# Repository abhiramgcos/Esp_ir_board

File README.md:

# ESP32 IR Blaster

**A Wi-Fi infrared remote you build yourself.** It learns the buttons of your existing remotes (TV, A/C, set-top
box, fan, LED strip) and plays them back from your phone, a script or Home Assistant.

<sub>KiCad 3D render of the v2.1.4 board, not a photo. The USB-C model is a stand-in for the HRO part.</sub>

## Features

* **Strong IR output:** two 940 nm LEDs driven at ~100 mA through a MOSFET, ≈8–10 m line-of-sight range.
* **On-board receiver:** a 38 kHz TSOP38238 for learning codes. The receiver and both IR LEDs face out of
  the same board edge, so one side of the board points at your devices.
* **One-click flashing:** USB-C with a CH340C USB-serial chip and auto-reset; no buttons, no adapter.
* **Ready-to-use firmware:**
  * web UI, REST API, captive-portal Wi-Fi setup, OTA updates;
  * stores decoded, A/C and raw codes.
* **Home Assistant via ESPHome:** native buttons, a climate entity for A/C, and send-code actions, from a
  prebuilt image you adopt in one click.
* **Robust power:** USB ESD protection, resettable fuse, diode-OR'd external 5 V input, 600 mA LDO.
* **Expansion:** I²C with pull-ups plus 8 free GPIOs on a 14-pin header, and a separate UART header.
* **Hand-solder friendly:** 0805/1206 passives, SOT-23/SOIC parts, and a value table printed on the back.
  Can also be ordered assembled.

## Hardware at a glance

| | |
|---|---|
| MCU | ESP32-WROOM-32E (4 MB flash, Wi-Fi + BT), PCB antenna overhanging the board edge |
| Power | USB-C 5 V or EXT 5 V header → SS14 diode-OR → AP2112K-3.3 (600 mA) |
| IR transmit | 2× Vishay TSAL6200 in series, lying flat and pointing out of the right edge; 18 Ω, AO3400A low-side switch on IO4 |
| IR receive | Vishay TSOP38238 (38 kHz) on IO16; dome faces the same edge as the LEDs |
| USB-serial | CH340C, DTR/RTS auto-reset (2× MMBT3904) |
| User I/O | RESET, BOOT and USER (IO13) buttons; green power LED; blue LED on IO2 |
| Headers | J3 UART (6-pin), J4 expansion (14-pin), J2 EXT 5V |
| PCB | 68 × 48 mm, 2 layers, 1.6 mm, 4× M2 holes, JLCPCB/PCBWay standard process |

<sub>The back carries the credits: inspired by T.K.V ([github.com/tkv-04](https://github.com/tkv-04),
[tkv.in.net](https://tkv.in.net)), designed by abhiramgcos ([github.com/abhiramgcos](https://github.com/abhiramgcos),
[abhiramg.in](https://abhiramg.in)).</sub>

<sub>The IR edge: the TSOP38238 receiver and both TSAL6200 LEDs (lying flat, leads bent 90°) face out of the
same side of the board.</sub>

### Copper layout

Two-layer board: signals on both sides, solid GND pour on both layers with via stitching, and a copper-free
strip under the ESP32 antenna. Colours follow KiCad: **red = top copper (F.Cu)**, **blue = bottom copper
(B.Cu)**, white = drills and vias.

<sub>Both copper layers overlaid with the ground pours hidden, so every trace and via is visible. Power nets
(VIN, 3V3, IR LED loop) use 0.5 mm tracks; signals use 0.25 mm; USB D+/D− and CC use 0.15 mm at the
connector.</sub>

| Top copper (F.Cu) | Bottom copper (B.Cu, viewed from below) |
|---|---|
|  |  |

Regenerate with `make copper`.

## Getting started

| Step | What to do | Guide |
|---|---|---|
| 1. Get a board | Upload `fab/esp_ir_board_v2_gerbers.zip` to JLCPCB or PCBWay (≈5 boards for a few dollars), optionally with SMD assembly | [esphome/README.md](esphome/README.md) | Home Assistant via ESPHome: adopt the prebuilt image or build your own config, learning codes, A/C climate |
| [docs/ORDERING.md](docs/ORDERING.md) |
| 2. Get the parts | BOM, what each part does, safe substitutes | [docs/COMPONENTS.md](docs/COMPONENTS.md) |
| 3. Assemble | Solder order and first power-up checks | [docs/COMPONENTS.md §3](docs/COMPONENTS.md#3-what-to-buy-for-hand-assembly) |
| 4. Flash | **Stand-alone firmware**: browser flasher (no install), Arduino IDE, or PlatformIO | [firmware/README.md](firmware/README.md) |
| 4b. …or Home Assistant | **ESPHome**: flash the prebuilt image, adopt it in HA, add your buttons | [esphome/README.md](esphome/README.md) |
| 5. Use | Join `ESP32-IR-Setup`, pick your Wi-Fi, open `http://irblaster.local` | [firmware/README.md#using-it](firmware/README.md#using-it) |
| Something wrong? | Power, USB, flashing, Wi-Fi and IR checks, step by step | [docs/TROUBLESHOOTING.md](docs/TROUBLESHOOTING.md) |

**Quickest flash:** download `esp32_ir_blaster_v2.1.1_full.bin` from
[Releases](https://github.com/abhiramgcos/Esp_ir_board/releases/latest). Open the
[ESP Tool web flasher](https://espressif.github.io/esptool-js/) in Chrome, connect to the CH340 port, and
program the file at address `0x0`.

## Pinout

| Function | GPIO | Notes |
|---|---|---|
| IR transmit | **IO4** | HIGH = LEDs on; the 38 kHz carrier is generated in software |
| IR receive | **IO16** | TSOP output, active low |
| Status LED (blue) | **IO2** | Strapping pin; the LED holds it low at boot, as required |
| USER button | **IO13** | Active low, 10 k pull-up |
| I²C | **IO21** SDA / **IO22** SCL | 4.7 k pull-ups on board |
| UART0 | IO1 TX / IO3 RX | Also on J3; an external adapter overrides the CH340 through 1 k |
| J4 expansion | VIN, 3V3, GND, SDA, SCL, IO18, 19, 23, 25, 26, 32, 33, 34, 35 | IO34/35 are input-only |

## Design notes

```mermaid
flowchart LR
  USB[USB-C] -->|D+/D-| ESD[USBLC6 ESD] --> CH[CH340C]
  USB -->|VBUS| F[PTC 0.75 A] --> D1[SS14]
  EXT[EXT 5V] --> D2[SS14]
  D1 --> VIN((VIN ≈4.5 V))
  D2 --> VIN
  VIN --> LDO[AP2112K-3.3] --> ESP[ESP32-WROOM-32E]
  CH -->|TX/RX, DTR/RTS auto-reset| ESP
  ESP -->|IO4| Q[AO3400A] --> IR[2× TSAL6200]
  VIN --> IR
  RX[TSOP38238] -->|IO16| ESP
```

* **IR drive.** The LEDs run from VIN, not from the 3.3 V rail: (4.5 V − 2 × 1.35 V) / 18 Ω ≈ 100 mA during
  carrier pulses. That's inside the TSAL6200 pulsed rating, and it keeps IR bursts from disturbing the
  ESP32 supply. C10 (22 µF) is the local reservoir.
* **3.3 V rail.** The AP2112K has 0.25 V dropout and 600 mA output, which leaves margin over ESP32 Wi-Fi peaks
  (~400–500 mA) even from the diode-dropped 4.5 V VIN.
* **Auto-reset.** This is the standard two-transistor DTR/RTS circuit, so esptool, the Arduino IDE and
  PlatformIO can enter the bootloader on their own. A 1 k resistor in the CH340 TX line lets an adapter on J3
  take over UART0.
* **Antenna.** The module's antenna overhangs the top edge by ≈5.5 mm, with no copper, tracks or vias under it
  on either layer. Leave the space free in an enclosure.

Full schematic: [PDF](hardware/docs/esp_ir_board_schematic.pdf) · [PNG](docs/img/v2.1_schematic.png).

## Development

### Repository layout

```
hardware/    KiCad 9 project (schematic, PCB, rules) + schematic/assembly PDFs
fab/         Gerbers + drills (zip), BOM, JLCPCB BOM/CPL       <- regenerated by `make fab`
firmware/    Stand-alone firmware: Arduino sketch + PlatformIO project
esphome/     ESPHome package, example config and factory image config for Home Assistant
gen/         Python generators: circuit.py is the single source of truth for parts and nets
tools/       Independent Gerber connectivity checker, offscreen 3D renderer
scripts/     esp.sh (behind `make`), silk preview
setup/       Toolchain installer (apt/pacman/dnf + Python venv)
docs/        Ordering, components, troubleshooting, build log, v1 review, images
v1/          Original v1 fab files (reference only)
```

### Toolchain

```bash
git clone https://github.com/abhiramgcos/Esp_ir_board.git && cd Esp_ir_board
./setup/install.sh            # KiCad 9, gerbv, librsvg, Python venv with pcbnew (asks for sudo once)
source .venv/bin/activate
make help                     # open | sch | pcb | 3d | copper | gerbers | render | check | bom | fab | rebuild
```

Details: [setup/README.md](setup/README.md), [scripts/README.md](scripts/README.md).

### Editing the design

There are two ways to make changes:

* **In KiCad.** Open `hardware/esp_ir_board.kicad_pro`, edit, then run `make fab && make check`.
* **From code.** Change `gen/circuit.py` (parts and nets) or `gen/placement.py` (positions). Then run
  `gen/build.sh`. It regenerates the schematic, places and routes the board with the built-in 2-layer router,
  pours copper, places silkscreen and runs DRC into `build/`, in about 5 minutes. Copy the result into
  `hardware/` once you're happy with it.

The routing comes from `gen/router.py`. It is DRC-clean and functional, but it is not hand-polished; touching
it up in KiCad is welcome.

### Verification

`make check` runs all of these. The table shows the current results.

| Check | Tool | Result (v2.1) |
|---|---|---|
| Netlist vs `circuit.py` | `gen/erc.py` | 162 pins, 41 nets, 0 problems |
| Electrical rules | `kicad-cli sch erc` | 0 errors |
| Design rules + schematic parity | `kicad-cli pcb drc` | 0 errors, 0 unconnected |
| Manufactured copper vs schematic | `tools/gerber_connectivity.py` on the Gerbers | 41 nets, 0 shorts, 0 opens, 162/162 pins |
| Firmware | `pio run` | builds without warnings |
| ESPHome configs | `esphome config` / `esphome compile` | valid, compiles |

The remaining DRC **warnings** are expected:
* silk clipped at the board edge, where the ESP32 and USB-C overhang on purpose;
* net-name prefix notes (`VIN` vs `/VIN`) from the generated schematic.

## Status

* v2.1.4 hardware and v2.1.1 firmware are complete and verified by the checks above. **No board has been
  manufactured yet**, so treat the first build as a prototype run.
* Every SMD part has a verified, in-stock LCSC number, so JLCPCB's BOM tool matches the whole BOM
  automatically. The through-hole parts (IR LEDs, TSOP, buttons, headers) are left for hand soldering.
* Always check part rotations in the fab's placement preview.

## Documentation

| Document | Contents |
|---|---|
| [firmware/README.md](firmware/README.md) | Flashing (web, Arduino IDE, PlatformIO), Wi-Fi setup, web UI, REST API, Home Assistant, OTA |
| [esphome/README.md](esphome/README.md) | Home Assistant via ESPHome: adopt the prebuilt image or build your own config, learning codes, A/C climate |
| [docs/ORDERING.md](docs/ORDERING.md) | JLCPCB and PCBWay, bare and assembled, step by step |
| [docs/COMPONENTS.md](docs/COMPONENTS.md) | BOM, the role of each part, drop-in alternatives, assembly order |
| [docs/TROUBLESHOOTING.md](docs/TROUBLESHOOTING.md) | Power, USB, flashing, boot, Wi-Fi and IR debugging |
| [docs/BUILD_LOG.md](docs/BUILD_LOG.md) | How the board was designed, step by step, with images |
| [CHANGELOG.md](CHANGELOG.md) | Version history (v1 → v2.0 → v2.1) |

## Credits

* Designed by **abhiramgcos**: [github.com/abhiramgcos](https://github.com/abhiramgcos) · [abhiramg.in](https://abhiramg.in)
* Inspired by **T.K.V**: [github.com/tkv-04](https://github.com/tkv-04) · [tkv.in.net](https://tkv.in.net)

## License

* **Hardware** (`hardware/`, `fab/`, `v1/`, docs and images): [CERN-OHL-P-2.0](LICENSES/CERN-OHL-P-2.0.txt).
* **Software** (`firmware/`, `esphome/`, `gen/`, `tools/`, `scripts/`, `setup/`): [MIT](LICENSES/MIT.txt).

You can build, modify and sell boards and derivatives, including commercially. Keep the copyright and license
notices, and point to this repository as the source. See [LICENSE](LICENSE) for details.

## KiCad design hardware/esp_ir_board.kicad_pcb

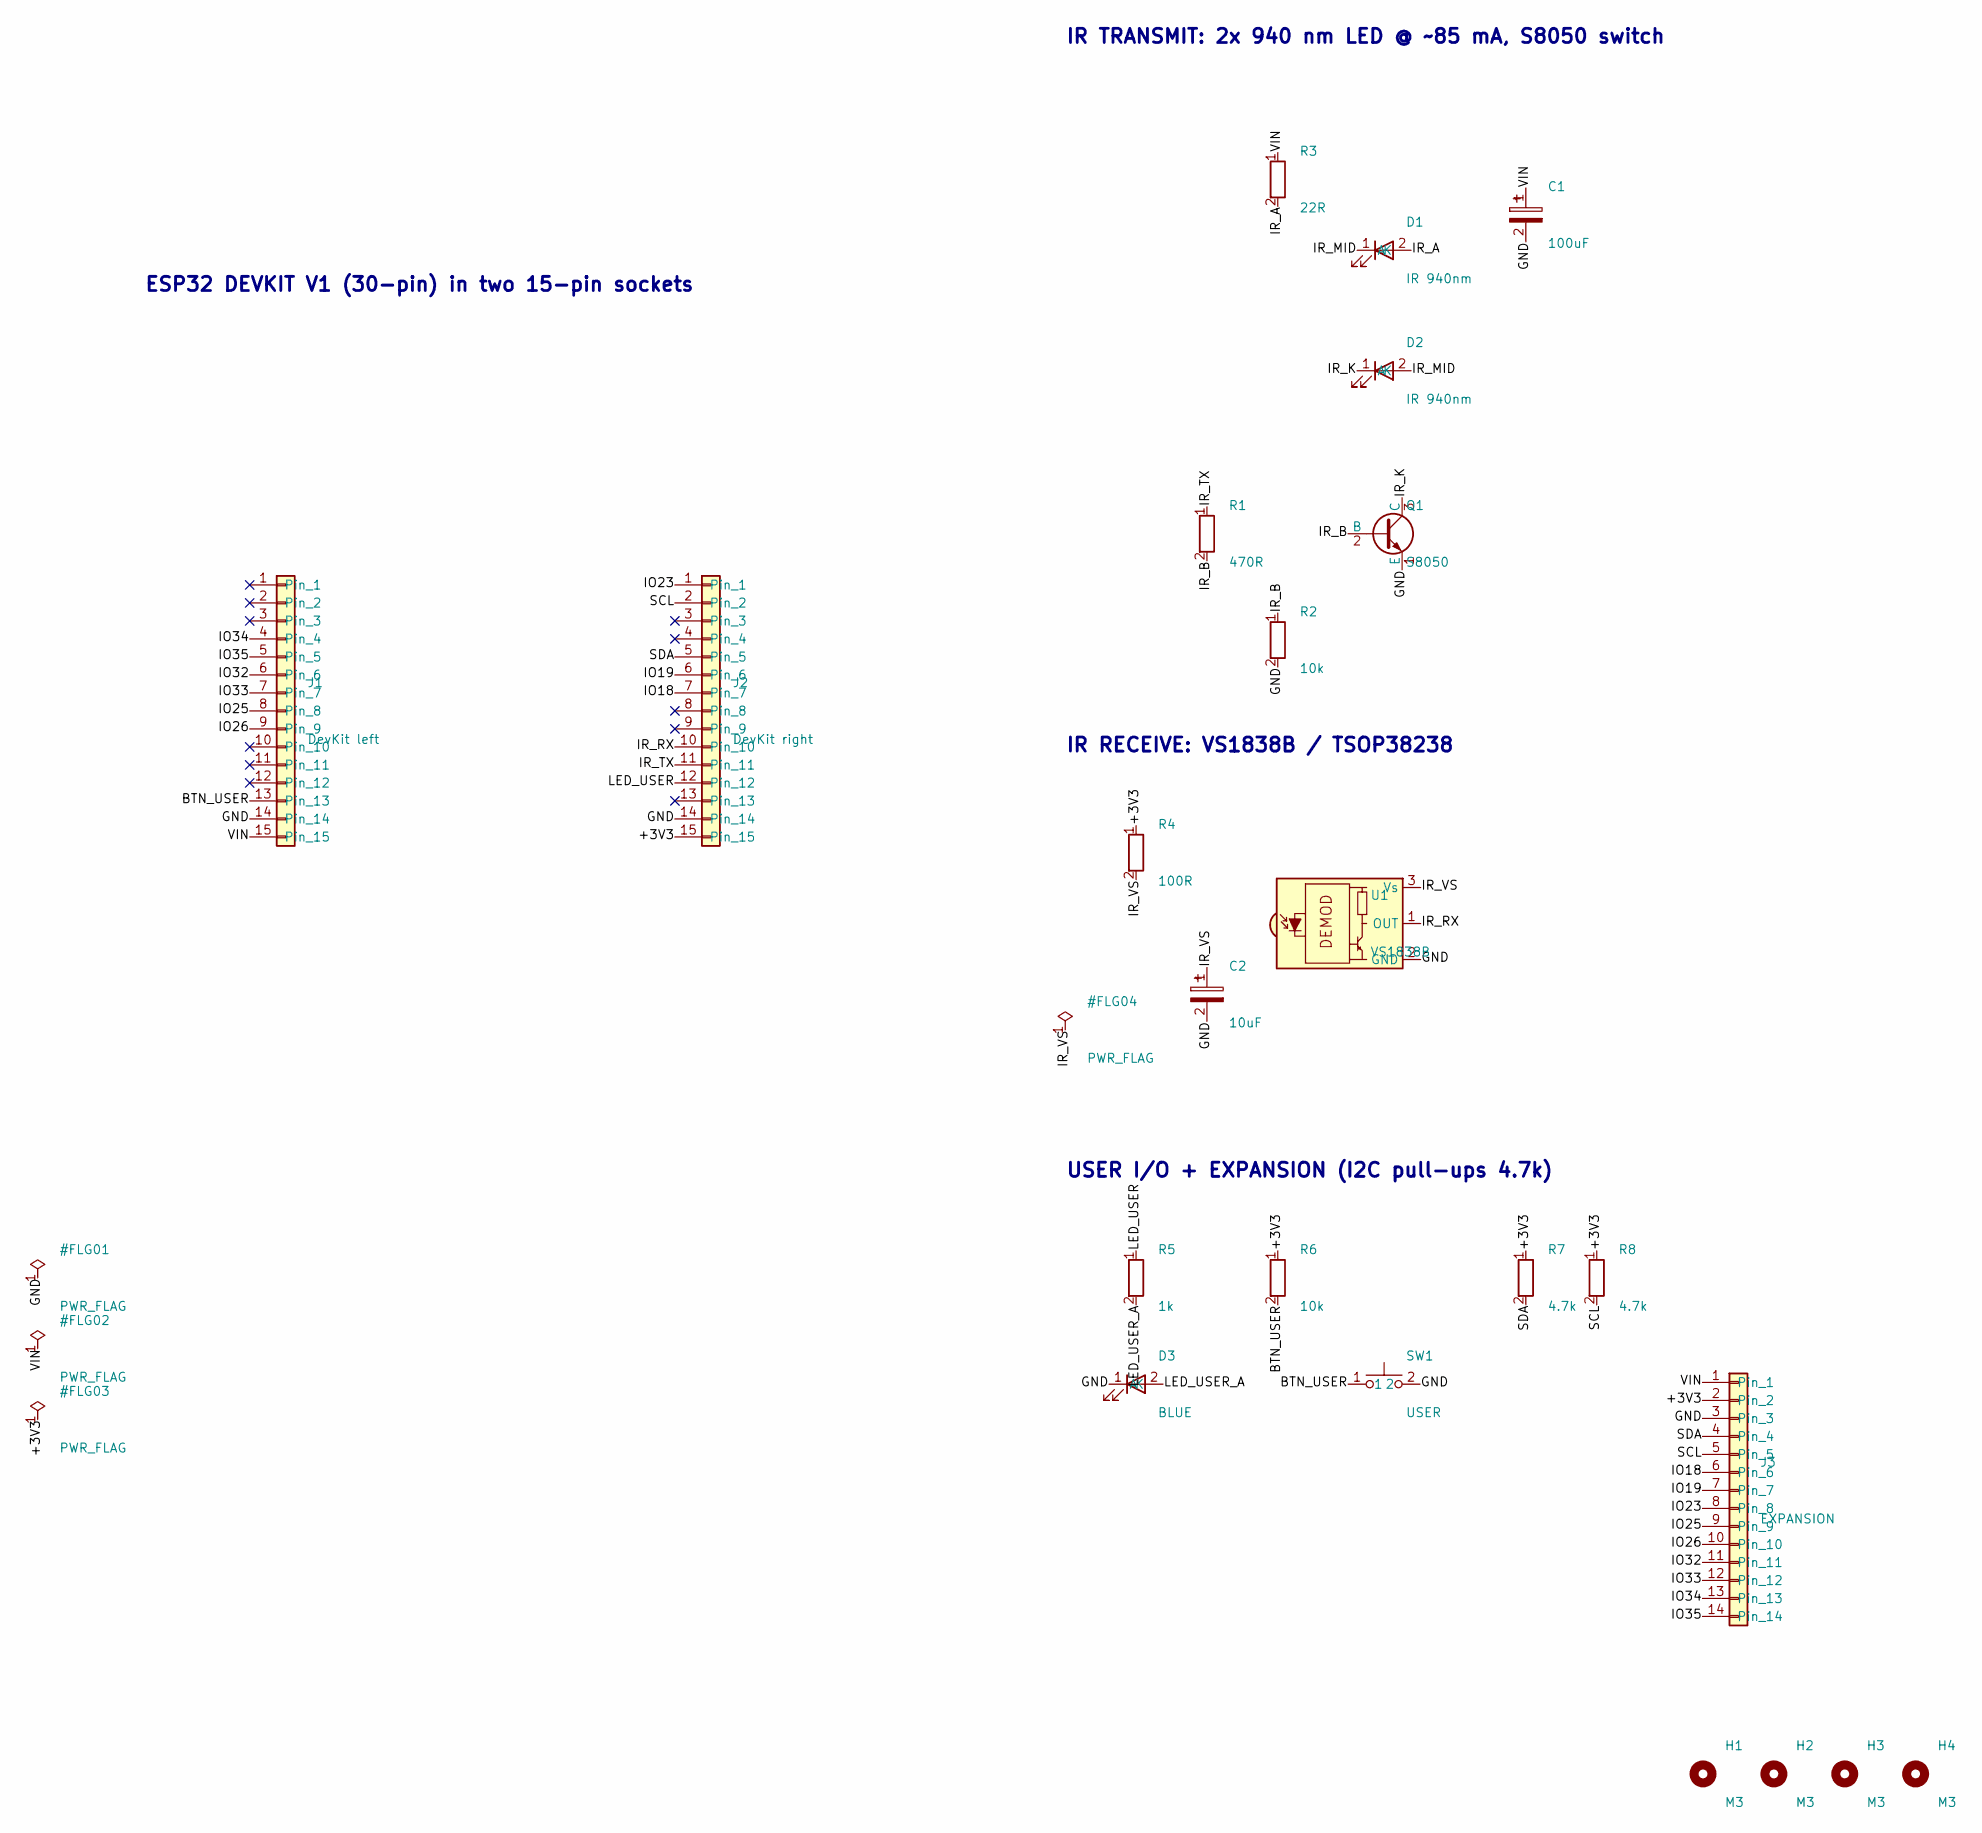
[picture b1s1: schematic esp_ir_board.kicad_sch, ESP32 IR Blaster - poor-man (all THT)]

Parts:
C1: 100uF; CP_Radial_D5.0mm_P2.00mm; MPN 100 uF 16 V electrolytic
C2: 10uF; CP_Radial_D5.0mm_P2.00mm; MPN 10 uF 16 V electrolytic
D1, D2: IR 940nm; LED_D5.0mm_Horizontal_O1.27mm_Z3.0mm_Clear; MPN 5 mm 940 nm IR LED (TSAL6200 or any "IR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
D3: BLUE; LED_D5.0mm; MPN 5 mm LED, any colour
H1, H2, H3, H4: M3; MountingHole_3.2mm_M3
J1: DevKit left; PinSocket_1x15_P2.54mm_Vertical; MPN 15-pin female header 2.54 mm
J2: DevKit right; PinSocket_1x15_P2.54mm_Vertical; MPN 15-pin female header 2.54 mm
J3: EXPANSION; PinHeader_1x14_P2.54mm_Vertical; MPN 14-pin male header 2.54 mm
Q1: S8050; TO-92_Inline_Wide; MPN S8050 or 2N2222A (TO-92, E-B-C)
R1: 470R; R_Axial_DIN0207_L6.3mm_D2.5mm_P7.62mm_Horizontal; MPN 470R 1/4 W axial
R2, R6: 10k; R_Axial_DIN0207_L6.3mm_D2.5mm_P7.62mm_Horizontal; MPN 10k 1/4 W axial
R3: 22R; R_Axial_DIN0207_L6.3mm_D2.5mm_P7.62mm_Horizontal; MPN 22R 1/4 W axial
R4: 100R; R_Axial_DIN0207_L6.3mm_D2.5mm_P7.62mm_Horizontal; MPN 100R 1/4 W axial
R5: 1k; R_Axial_DIN0207_L6.3mm_D2.5mm_P7.62mm_Horizontal; MPN 1k 1/4 W axial
R7, R8: 4.7k; R_Axial_DIN0207_L6.3mm_D2.5mm_P7.62mm_Horizontal; MPN 4.7k 1/4 W axial
SW1: USER; SW_PUSH_6mm_H5mm; MPN 6x6 mm tactile switch
U1: VS1838B; Vishay_MOLD-3Pin; MPN VS1838B or TSOP38238 (pins OUT-GND-VCC)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

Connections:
+3V3: J2.15, J3.2, R4.1, R6.1, R7.1, R8.1
BTN_USER: J1.13, R6.2, SW1.1
GND: C1.2, C2.2, D3.1 (K), J1.14, J2.14, J3.3, Q1.1 (E), R2.2, SW1.2, U1.2 (GND)
IO18: J2.7, J3.6
IO19: J2.6, J3.7
IO23: J2.1, J3.8
IO25: J1.8, J3.9
IO26: J1.9, J3.10
IO32: J1.6, J3.11
IO33: J1.7, J3.12
IO34: J1.4, J3.13
IO35: J1.5, J3.14
IR_A: D1.2 (A), R3.2
IR_B: Q1.2 (B), R1.2, R2.1
IR_K: D2.1 (K), Q1.3 (C)
IR_MID: D1.1 (K), D2.2 (A)
IR_RX: J2.10, U1.1 (OUT)
IR_TX: J2.11, R1.1
IR_VS: C2.1, R4.2, U1.3 (Vs)
LED_USER: J2.12, R5.1
LED_USER_A: D3.2 (A), R5.2
SCL: J2.2, J3.5, R8.2
SDA: J2.5, J3.4, R7.2
VIN: C1.1, J1.15, J3.1, R3.1

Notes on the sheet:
ESP32 DEVKIT V1 (30-pin) in two 15-pin sockets
IR TRANSMIT: 2x 940 nm LED @ ~85 mA, S8050 switch
IR RECEIVE: VS1838B / TSOP38238
USER I/O + EXPANSION (I2C pull-ups 4.7k)

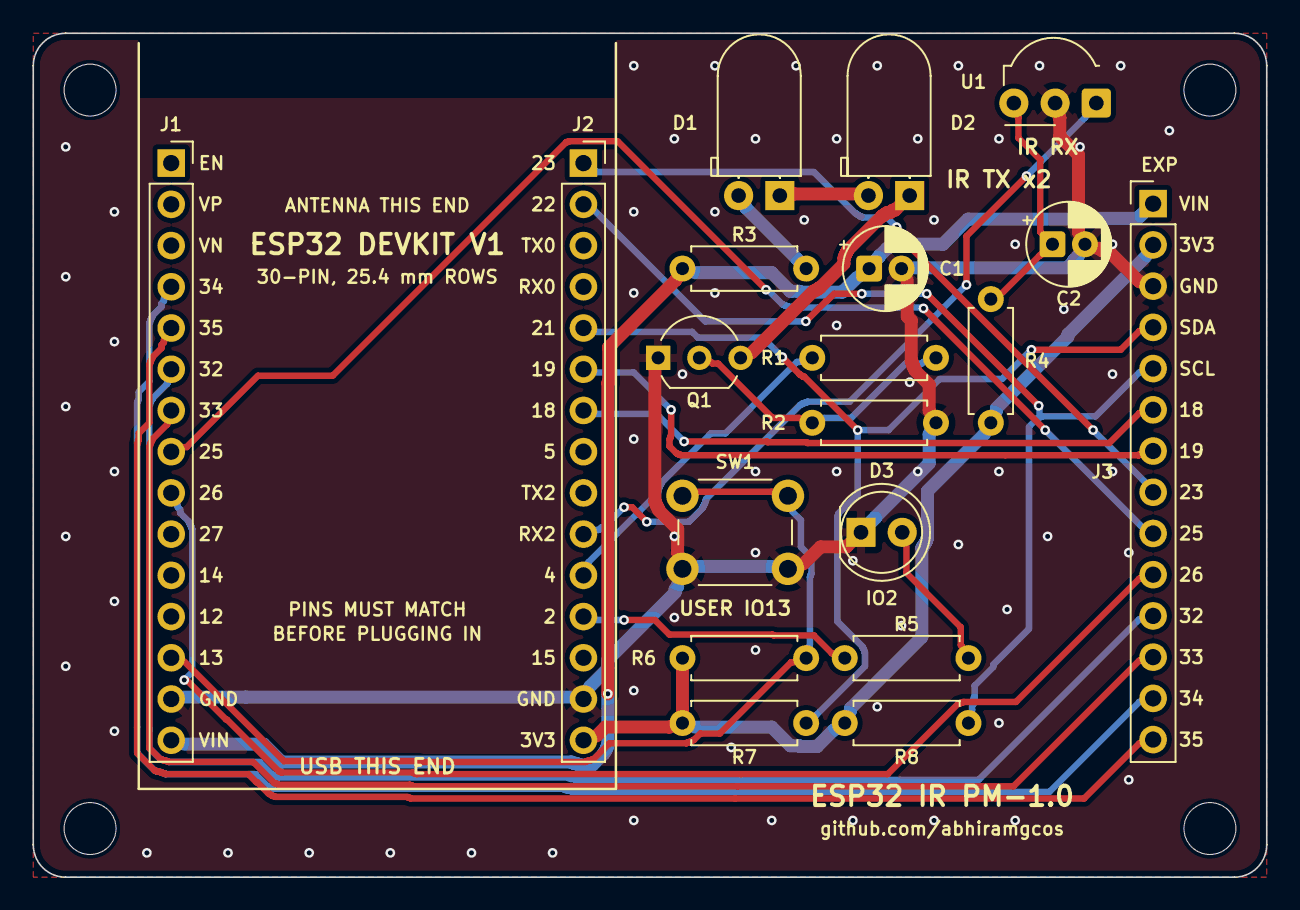
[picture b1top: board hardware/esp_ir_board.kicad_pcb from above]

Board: 2 copper layers, 76.0 x 52.0 mm, 23 parts (0 on the bottom side), 24 nets.

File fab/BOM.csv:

Qty,Designators,Value,What to buy,Footprint
1,J1,DevKit left,15-pin female header 2.54 mm,PinSocket_1x15_P2.54mm_Vertical
1,J2,DevKit right,15-pin female header 2.54 mm,PinSocket_1x15_P2.54mm_Vertical
1,R3,22R,22R 1/4 W axial,R_Axial_DIN0207_L6.3mm_D2.5mm_P7.62mm_Horizontal
2,"D1,D2",IR 940nm,"5 mm 940 nm IR LED (TSAL6200 or any ""IR transmitter LED"")",LED_D5.0mm_Horizontal_O1.27mm_Z3.0mm_Clear
1,Q1,S8050,"S8050 or 2N2222A (TO-92, E-B-C)",TO-92_Inline_Wide
1,R1,470R,470R 1/4 W axial,R_Axial_DIN0207_L6.3mm_D2.5mm_P7.62mm_Horizontal
2,"R2,R6",10k,10k 1/4 W axial,R_Axial_DIN0207_L6.3mm_D2.5mm_P7.62mm_Horizontal
1,C1,100uF,100 uF 16 V electrolytic,CP_Radial_D5.0mm_P2.00mm
1,U1,VS1838B,VS1838B or TSOP38238 (pins OUT-GND-VCC). NOT TSOP1738: different pinout,Vishay_MOLD-3Pin
1,R4,100R,100R 1/4 W axial,R_Axial_DIN0207_L6.3mm_D2.5mm_P7.62mm_Horizontal
1,C2,10uF,10 uF 16 V electrolytic,CP_Radial_D5.0mm_P2.00mm
1,R5,1k,1k 1/4 W axial,R_Axial_DIN0207_L6.3mm_D2.5mm_P7.62mm_Horizontal
1,D3,BLUE,"5 mm LED, any colour",LED_D5.0mm
1,SW1,USER,6x6 mm tactile switch,SW_PUSH_6mm_H5mm
2,"R7,R8",4.7k,4.7k 1/4 W axial,R_Axial_DIN0207_L6.3mm_D2.5mm_P7.62mm_Horizontal
1,J3,EXPANSION,14-pin male header 2.54 mm,PinHeader_1x14_P2.54mm_Vertical
1,(plugs into J1/J2),ESP32 DevKit V1,"ESP32 DevKit V1, 30-pin (DOIT layout), rows 25.4 mm apart",-

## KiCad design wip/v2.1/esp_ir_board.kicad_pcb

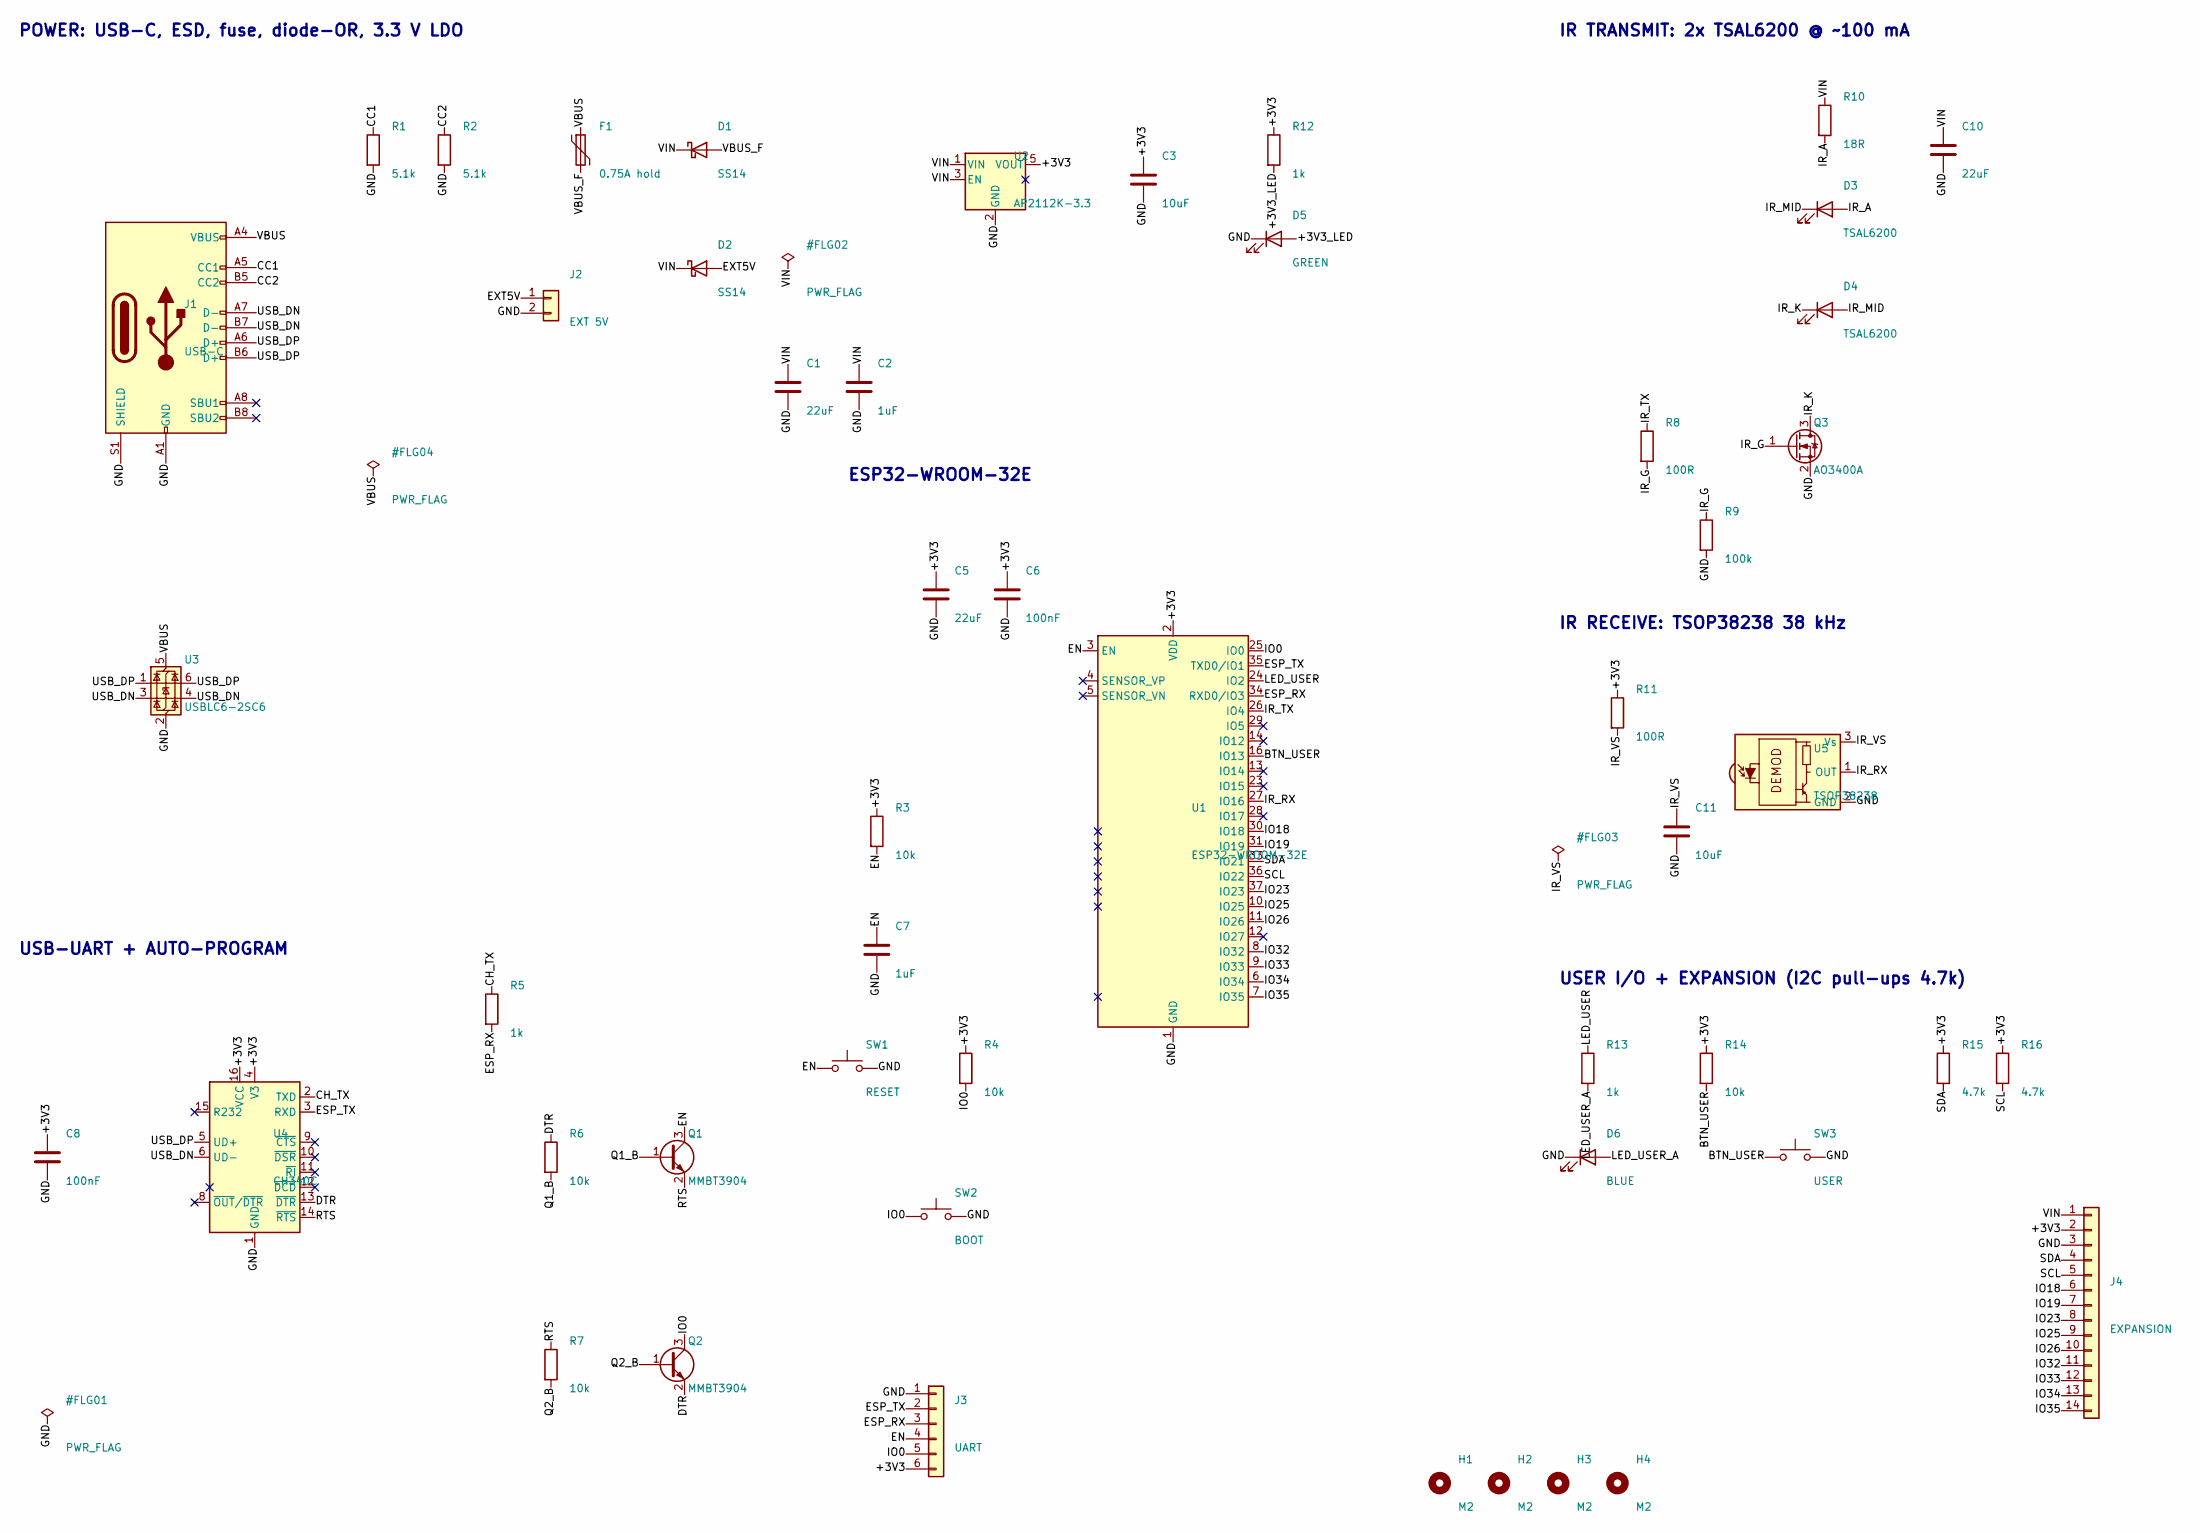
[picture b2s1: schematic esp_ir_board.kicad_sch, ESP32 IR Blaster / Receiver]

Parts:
C1, C5, C10: 22uF; C_1206_3216Metric_Pad1.33x1.80mm_HandSolder; MPN 22uF 16V X5R 1206
C2, C7: 1uF; C_0805_2012Metric_Pad1.18x1.45mm_HandSolder; LCSC C28323
C3, C11: 10uF; C_0805_2012Metric_Pad1.18x1.45mm_HandSolder; LCSC C15850
C6, C8: 100nF; C_0805_2012Metric_Pad1.18x1.45mm_HandSolder; LCSC C49678
D1, D2: SS14; D_SMA_Handsoldering; MPN SS14; LCSC C2480
D3, D4: TSAL6200; LED_D5.0mm; MPN Vishay TSAL6200
D5: GREEN; LED_0805_2012Metric_Pad1.15x1.40mm_HandSolder; MPN 0805 green LED
D6: BLUE; LED_0805_2012Metric_Pad1.15x1.40mm_HandSolder; MPN 0805 blue LED
F1: 0.75A hold; Fuse_1206_3216Metric_Pad1.42x1.75mm_HandSolder; MPN 1206 PTC resettable fuse, 0.75 A hold, 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
H1, H2, H3, H4: M2; MountingHole_2.2mm_M2
J1: USB-C; USB_C_Receptacle_HRO_TYPE-C-31-M-12; MPN HRO TYPE-C-31-M-12; LCSC C165948
J2: EXT 5V; PinHeader_1x02_P2.54mm_Vertical; MPN 2.54 mm header 1x2
J3: UART; PinHeader_1x06_P2.54mm_Vertical; MPN 2.54 mm header 1x6
J4: EXPANSION; PinHeader_1x14_P2.54mm_Vertical; MPN 2.54 mm header 1x14
Q1, Q2: MMBT3904; SOT-23; MPN MMBT3904; LCSC C20526
Q3: AO3400A; SOT-23; MPN AO3400A; LCSC C20917
R1, R2: 5.1k; R_0805_2012Metric_Pad1.20x1.40mm_HandSolder; LCSC C27834
R3, R4, R6, R7, R14: 10k; R_0805_2012Metric_Pad1.20x1.40mm_HandSolder; LCSC C17414
R5, R12, R13: 1k; R_0805_2012Metric_Pad1.20x1.40mm_HandSolder; LCSC C17513
R8, R11: 100R; R_0805_2012Metric_Pad1.20x1.40mm_HandSolder; LCSC C17408
R9: 100k; R_0805_2012Metric_Pad1.20x1.40mm_HandSolder; LCSC C149504
R10: 18R; R_1206_3216Metric_Pad1.30x1.75mm_HandSolder; MPN 18 ohm 1206 1%
R15, R16: 4.7k; R_0805_2012Metric_Pad1.20x1.40mm_HandSolder; LCSC C17673
SW1: RESET; SW_PUSH_6mm_H5mm; MPN 6x6 mm tactile THT
SW2: BOOT; SW_PUSH_6mm_H5mm; MPN 6x6 mm tactile THT
SW3: USER; SW_PUSH_6mm_H5mm; MPN 6x6 mm tactile THT
U1: ESP32-WROOM-32E; ESP32-WROOM-32D; MPN ESP32-WROOM-32E-N4
U2: AP2112K-3.3; SOT-23-5; MPN AP2112K-3.3TRG1; LCSC C51118
U3: USBLC6-2SC6; SOT-23-6; MPN USBLC6-2SC6; LCSC C7519
U4: CH340C; SOIC-16_3.9x9.9mm_P1.27mm; MPN CH340C; LCSC C84681
U5: TSOP38238; Vishay_MOLD-3Pin; MPN Vishay TSOP38238

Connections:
+3V3: C3.1, C5.1, C6.1, C8.1, J3.6, J4.2, R3.1, R4.1, R11.1, R12.1, R14.1, R15.1, R16.1, U1.2 (VDD), U2.5 (VOUT), U4.4 (V3), U4.16 (VCC)
+3V3_LED: D5.2 (A), R12.2
BTN_USER: R14.2, SW3.1, U1.16 (IO13)
CC1: J1.A5 (CC1), R1.1
CC2: J1.B5 (CC2), R2.1
CH_TX: R5.1, U4.2 (TXD)
DTR: Q2.2 (E), R6.1, U4.13 (~DTR)
EN: C7.1, J3.4, Q1.3 (C), R3.2, SW1.1, U1.3 (EN)
ESP_RX: J3.3, R5.2, U1.34 (RXD0/IO3)
ESP_TX: J3.2, U1.35 (TXD0/IO1), U4.3 (RXD)
EXT5V: D2.2 (A), J2.1
GND: C1.2, C2.2, C3.2, C5.2, C6.2, C7.2, C8.2, C10.2, C11.2, D5.1 (K), D6.1 (K), J1.A1 (GND), J1.A12 (GND), J1.B1 (GND), J1.B12 (GND), J1.S1 (SHIELD), J2.2, J3.1, J4.3, Q3.2 (S), R1.2, R2.2, R9.2, SW1.2, SW2.2, SW3.2, U1.1 (GND), U1.15 (GND), U1.38 (GND), U1.39 (GND), U2.2 (GND), U3.2 (GND), U4.1 (GND), U5.2 (GND)
IO0: J3.5, Q2.3 (C), R4.2, SW2.1, U1.25 (IO0)
IO18: J4.6, U1.30 (IO18)
IO19: J4.7, U1.31 (IO19)
IO23: J4.8, U1.37 (IO23)
IO25: J4.9, U1.10 (IO25)
IO26: J4.10, U1.11 (IO26)
IO32: J4.11, U1.8 (IO32)
IO33: J4.12, U1.9 (IO33)
IO34: J4.13, U1.6 (IO34)
IO35: J4.14, U1.7 (IO35)
IR_A: D3.2 (A), R10.2
IR_G: Q3.1 (G), R8.2, R9.1
IR_K: D4.1 (K), Q3.3 (D)
IR_MID: D3.1 (K), D4.2 (A)
IR_RX: U1.27 (IO16), U5.1 (OUT)
IR_TX: R8.1, U1.26 (IO4)
IR_VS: C11.1, R11.2, U5.3 (Vs)
LED_USER: R13.1, U1.24 (IO2)
LED_USER_A: D6.2 (A), R13.2
Q1_B: Q1.1 (B), R6.2
Q2_B: Q2.1 (B), R7.2
RTS: Q1.2 (E), R7.1, U4.14 (~RTS)
SCL: J4.5, R16.2, U1.36 (IO22)
SDA: J4.4, R15.2, U1.33 (IO21)
USB_DN: J1.A7 (D-), J1.B7 (D-), U3.3 (I/O2), U3.4 (I/O2), U4.6 (UD-)
USB_DP: J1.A6 (D+), J1.B6 (D+), U3.1 (I/O1), U3.6 (I/O1), U4.5 (UD+)
VBUS: F1.1, J1.A4 (VBUS), J1.A9 (VBUS), J1.B4 (VBUS), J1.B9 (VBUS), U3.5 (VBUS)
VBUS_F: D1.2 (A), F1.2
VIN: C1.1, C2.1, C10.1, D1.1 (K), D2.1 (K), J4.1, R10.1, U2.1 (VIN), U2.3 (EN)

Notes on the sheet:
POWER: USB-C, ESD, fuse, diode-OR, 3.3 V LDO
USB-UART + AUTO-PROGRAM
ESP32-WROOM-32E
IR TRANSMIT: 2x TSAL6200 @ ~100 mA
IR RECEIVE: TSOP38238 38 kHz
USER I/O + EXPANSION (I2C pull-ups 4.7k)

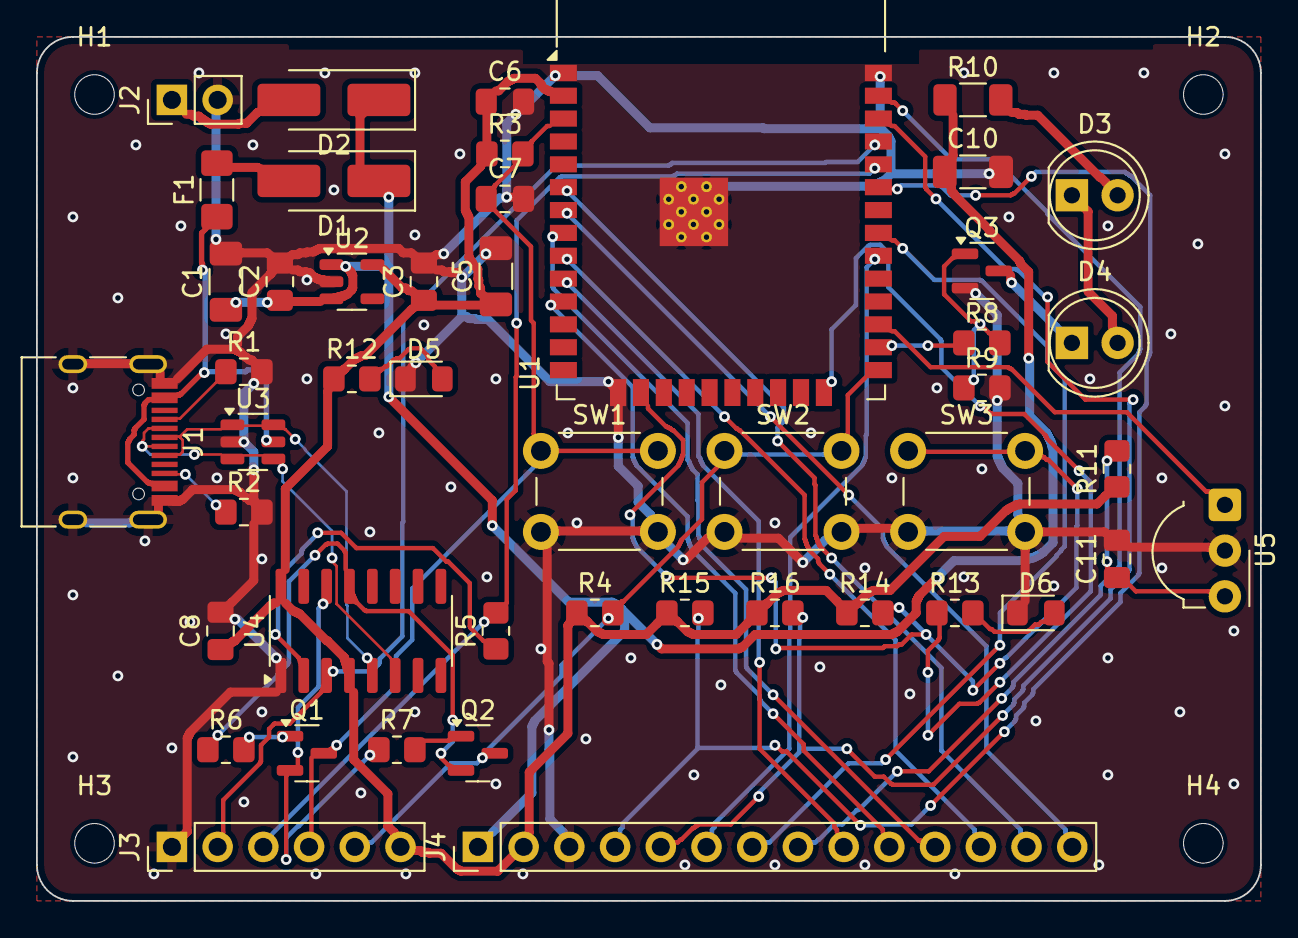
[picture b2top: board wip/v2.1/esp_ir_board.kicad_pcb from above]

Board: 2 copper layers, 68.0 x 48.0 mm, 51 parts (0 on the bottom side), 41 nets.

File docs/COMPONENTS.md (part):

# Components: what each part does, what to buy, and safe alternatives

**Board:** ESP32 IR Blaster/Receiver v2.1.4, 68 × 48 mm, 2 layers, 51 parts.

The machine-readable BOM is in `fab/BOM_full.csv`; the JLCPCB-format BOM and pick-and-place files are in
`fab/`. Values come from [`gen/circuit.py`](../gen/circuit.py), the single source of truth for the design.

**Hand-solder friendly.** All passives are 0805 or 1206 with the long `_HandSolder` pads. The ICs are SOT-23,
SOT-23-5/6, SOIC-16 and the ESP32 module (castellated pads). Everything else is through-hole.

> "Alternative" means **drop-in**: same footprint and pinout, no PCB change. Parts that look similar but
> do **not** fit are listed too, marked *no*.

## 1. Bill of materials

| Ref | Qty | Part | Package | Job on this board | LCSC # |
|---|---|---|---|---|---|
| U1 | 1 | **ESP32-WROOM-32E-N4** | module | Wi-Fi MCU, 4 MB flash | C701341 |
| U4 | 1 | **CH340C** | SOIC-16 | USB ↔ serial for flashing; internal clock (no crystal) | C84681 |
| U2 | 1 | **AP2112K-3.3TRG1** | SOT-23-5 | 3.3 V LDO, 600 mA | C51118 |
| U3 | 1 | **USBLC6-2SC6** | SOT-23-6 | ESD protection on USB D+/D− | C7519 |
| U5 | 1 | **Vishay TSOP38238** | 3-pin THT | IR receiver, 38 kHz demodulator → IO16; dome faces out of the right edge | C141632 |
| Q1, Q2 | 2 | **MMBT3904** | SOT-23 | DTR/RTS auto-reset into the bootloader | C20526 |
| Q3 | 1 | **AO3400A** | SOT-23 | N-MOSFET low-side switch for the IR LEDs | C20917 |
| D1, D2 | 2 | **SS14** | SMA | Schottky "OR" of USB 5 V and EXT 5 V (no back-feeding) | C2480 |
| D3, D4 | 2 | **Vishay TSAL6200** | 5 mm THT, **lying flat** | 940 nm IR LEDs in series, ~100 mA pulses; leads bent 90°, lenses point out of the right edge | C55528 |
| D5 | 1 | LED green (KENTO KT-0805G) | 0805 | power indicator | C2297 |
| D6 | 1 | LED blue (KENTO KT-0805B) | 0805 | user LED on IO2 | C2293 |
| F1 | 1 | PTC fuse, 0.75 A hold, 8 V (PTTC SMD1206P075TFT) | 1206 | USB over-current protection | C545214 |
| J1 | 1 | **HRO TYPE-C-31-M-12** | USB-C 16P SMD | power + programming | C165948 |
| J2 | 1 | pin header 1×2, 2.54 mm | THT | external 5 V input | – |
| J3 | 1 | pin header 1×6, 2.54 mm | THT | UART: GND TX RX EN IO0 3V3 | – |
| J4 | 1 | pin header 1×14, 2.54 mm | THT | expansion: VIN 3V3 GND SDA SCL 18 19 23 25 26 32 33 34 35 | – |
| SW1–SW3 | 3 | tactile switch 6×6 mm, H 5 mm | THT | RESET (EN), BOOT (IO0), USER (IO13) | – |
| R10 | 1 | 18 Ω 1 % (Yageo RC1206FR-0718RL) | **1206** | IR LED current: (4.5 V − 2×1.35 V) / 18 Ω ≈ 100 mA | C137378 |
| R1, R2 | 2 | 5.1 kΩ | 0805 | USB-C CC pull-downs (asks the charger for 5 V) | C27834 |
| R3, R4, R6, R7, R14 | 5 | 10 kΩ | 0805 | EN/IO0/button pull-ups, transistor base resistors | C17414 |
| R5, R12, R13 | 3 | 1 kΩ | 0805 | CH340 TX series, LED resistors | C17513 |
| R8, R11 | 2 | 100 Ω | 0805 | MOSFET gate resistor, TSOP supply filter | C17408 |
| R9 | 1 | 100 kΩ | 0805 | MOSFET gate pull-down (LEDs off during boot) | C149504 |
| R15, R16 | 2 | 4.7 kΩ | 0805 | I²C pull-ups | C17673 |
| C1, C5, C10 | 3 | 22 µF 25 V X5R (Samsung CL31A226KAHNNNE) | **1206** | bulk: VIN, 3V3 at the ESP32, IR LED reservoir | C12891 |
| C3, C11 | 2 | 10 µF 25 V X5R | 0805 | LDO output, TSOP supply filter | C15850 |
| C2, C7 | 2 | 1 µF 50 V X7R | 0805 | LDO input, EN reset delay | C28323 |
| C6, C8 | 2 | 100 nF 50 V X7R | 0805 | decoupling (ESP32, CH340) | C49678 |
| H1–H4 | 4 | M2 mounting holes | – | – | – |

Every LCSC number was checked against JLCPCB's parts library on 2026-11-20, and all were in stock. Stock and
Basic/Extended status change over time, so JLC's BOM tool has the final word. Parts with a "–" (headers,
buttons) are generic through-hole parts you solder yourself.

**Extra parts to buy:**
* 2.54 mm female headers if you want plug-in modules on J4.
* 4× M2 screws and standoffs.
* A USB-C cable *with data lines*. Some charge-only cables don't work for flashing.

## 2. Alternatives, part by part

### ESP32 module (U1)

| Option | Notes |
|---|---|
| ESP32-WROOM-32E-N4 | Default. 4 MB flash, PCB antenna, rev 3 silicon. |
| ESP32-WROOM-32E-N8 / -N16 | Drop-in, more flash. |
| ESP32-WROOM-32D / ESP32-WROOM-32 | Drop-in (older silicon; works with this firmware). |
| ESP32-WROOM-32UE | Drop-in, but U.FL connector for an external antenna. Good inside a metal box. |
| ESP32-C3 / S3 / C6 modules | *No*: different pinout and footprint. |

### USB-serial (U4)

| Option | Notes |
|---|---|
| CH340C | Default. Built-in oscillator. |
| CH340G | *No*: same SOIC-16, but **needs a 12 MHz crystal** on pins 7/8. |
| CH340K, CP2102N, FT231X | *No*: different packages and pinouts. |

Linux and macOS have CH340 drivers built in. On Windows 10/11 the driver installs automatically or from
wch-ic.com.

### 3.3 V regulator (U2)

All of these use the same SOT-23-5 pinout as AP2112K: 1 VIN, 2 GND, 3 EN, 4 NC, 5 VOUT.

| Option | Notes |
|---|---|
| AP2112K-3.3 (600 mA) | Default. |
| ME6211C33M5G (500 mA) | Cheap and common at LCSC. |
| XC6220B331MR (700 mA) | |
| RT9013-33**GB** (500 mA) | The **GB** suffix has pin 4 NC. The PB version has a bypass pin, which is also OK. |
| AMS1117-3.3 | *No*: SOT-223 package, ~1.1 V dropout is too much from a 4.5 V VIN. |

ESP32 Wi-Fi bursts draw about 350–500 mA, so don't use regulators under 500 mA (e.g. MCP1700, HT7333).

### USB ESD (U3)

USBLC6-2SC6 (ST) is the default, and pin-compatible copies are sold under the same name by Techpublic, UMW
and others.

The board also works without U3 if you bridge the D+/D− pads straight through:
* pin 1 → pin 6
* pin 3 → pin 4

This loses ESD protection. Not recommended for a board you'll plug in often.

### IR LEDs (D3, D4)

| Option | Notes |
|---|---|
| TSAL6200 (940 nm, ±17°, 100 mA) | Default. Good range and spread. |
| TSAL6100 (±10°) | Longer range, narrower beam. |
| TSAL6400 (±25°) | Wider beam, slightly less range. |
| Any 5 mm **940 nm** IR LED rated ≥100 mA, Vf ≈1.2–1.5 V | e.g. generic "IR333" types. |
| 850 nm LEDs | *No*: most TV/AC receivers are far less sensitive at 850 nm. |

**Polarity:** the longer leg is the anode (+). The flat side of the rim is the cathode, which matches the
square pad on the PCB.

### IR receiver (U5)

| Option | Notes |
|---|---|
| TSOP38238 | Default. Pinout 1 OUT, 2 GND, 3 VS, matching the footprint. |
| TSOP4838 | Same pinout, older series. |
| TSOP38438 | Same pinout, AGC4: better for A/C remotes with long frames. |
| VS1838B / HX1838 | Same OUT-GND-VCC order and very cheap; shorter range and more noise. |
| TSOP38236 / 38240 / 38256 | Use when your remotes are 36, 40 or 56 kHz. |
| TSOP1838, KY-022 modules, some no-name parts | *Check first*: several have VS and GND swapped. |

### Transistors

| Part | Options |
|---|---|
| Q1, Q2 (NPN) | MMBT3904 (default), MMBT2222A, S8050 (J3Y), BC847. All SOT-23 with 1 B, 2 E, 3 C. |
| Q3 (N-MOSFET, logic level at 3.3 V gate) | AO3400A (default), AO3402, SI2302CDS, IRLML6344, IRLML2502. All SOT-23 with 1 G, 2 S, 3 D. |

Avoid 2N7002 for Q3: its R<sub>DS(on)</sub> at 3.3 V gate drive is too high for 100 mA pulses.

### Diodes and fuse

| Part | Options |
|---|---|
| D1, D2 | SS14 (default), SS16, SS24, SS34, B140, MBRA140. All SMA Schottky, ≥1 A. SOD-123 parts (e.g. 1N5819W) do not fit. |
| F1 | Any 1206 PTC with 0.5–1.1 A hold and ≥6 V, e.g. Bourns MF-NSMF075, Littelfuse 1206L075. In a pinch, a 0 Ω 1206 jumper works (no over-current protection). |

### Passives, LEDs, buttons, headers

* **Resistors:** any 0805 1 % thick film. R10 should be 1206, rated at least 0.25 W.
* **Capacitors:**
  * X5R or X7R ceramic, rated ≥10 V (16 V preferred for the 22 µF). Don't use Y5V.
  * The 22 µF parts must be 1206.
  * Any capacitor can go one size up in value (e.g. 10 µF → 22 µF) without harm.
* **LEDs (D5, D6):** any 0805 colour. Change R12/R13 (1 kΩ) to adjust brightness. The cathode mark faces the
  "–"/bar on the silkscreen.
* **Buttons:** any 6×6 mm 4-pin THT tactile switch, any height (4.3 / 5 / 7 / 9.5 mm).
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

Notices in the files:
README.md:
License: CERN-OHL-P / MIT
